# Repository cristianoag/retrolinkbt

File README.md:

# RetroLinkBT
Simple adapter to allow the use of bluetooth joysticks with retro computers

## License 

This work is licensed under a [Creative Commons Attribution-NonCommercial-ShareAlike 4.0 International License](http://creativecommons.org/licenses/by-nc-sa/4.0/).

* If you remix, transform, or build upon the material, you must distribute your contributions under the same license as the original.
* You may not use the material for commercial purposes.
* You must give appropriate credit, provide a link to the license, and indicate if changes were made. You may do so in any reasonable manner, but not in any way that suggests the licensor endorses you or your use.

**ATTENTION**

This project was made for the retro community and not for commercial purposes. So only retro hardware forums and individual people can build this project.

THE SALE OF ANY PART OF THIS PROJECT WITHOUT EXPRESS AUTHORIZATION IS PROHIBITED!

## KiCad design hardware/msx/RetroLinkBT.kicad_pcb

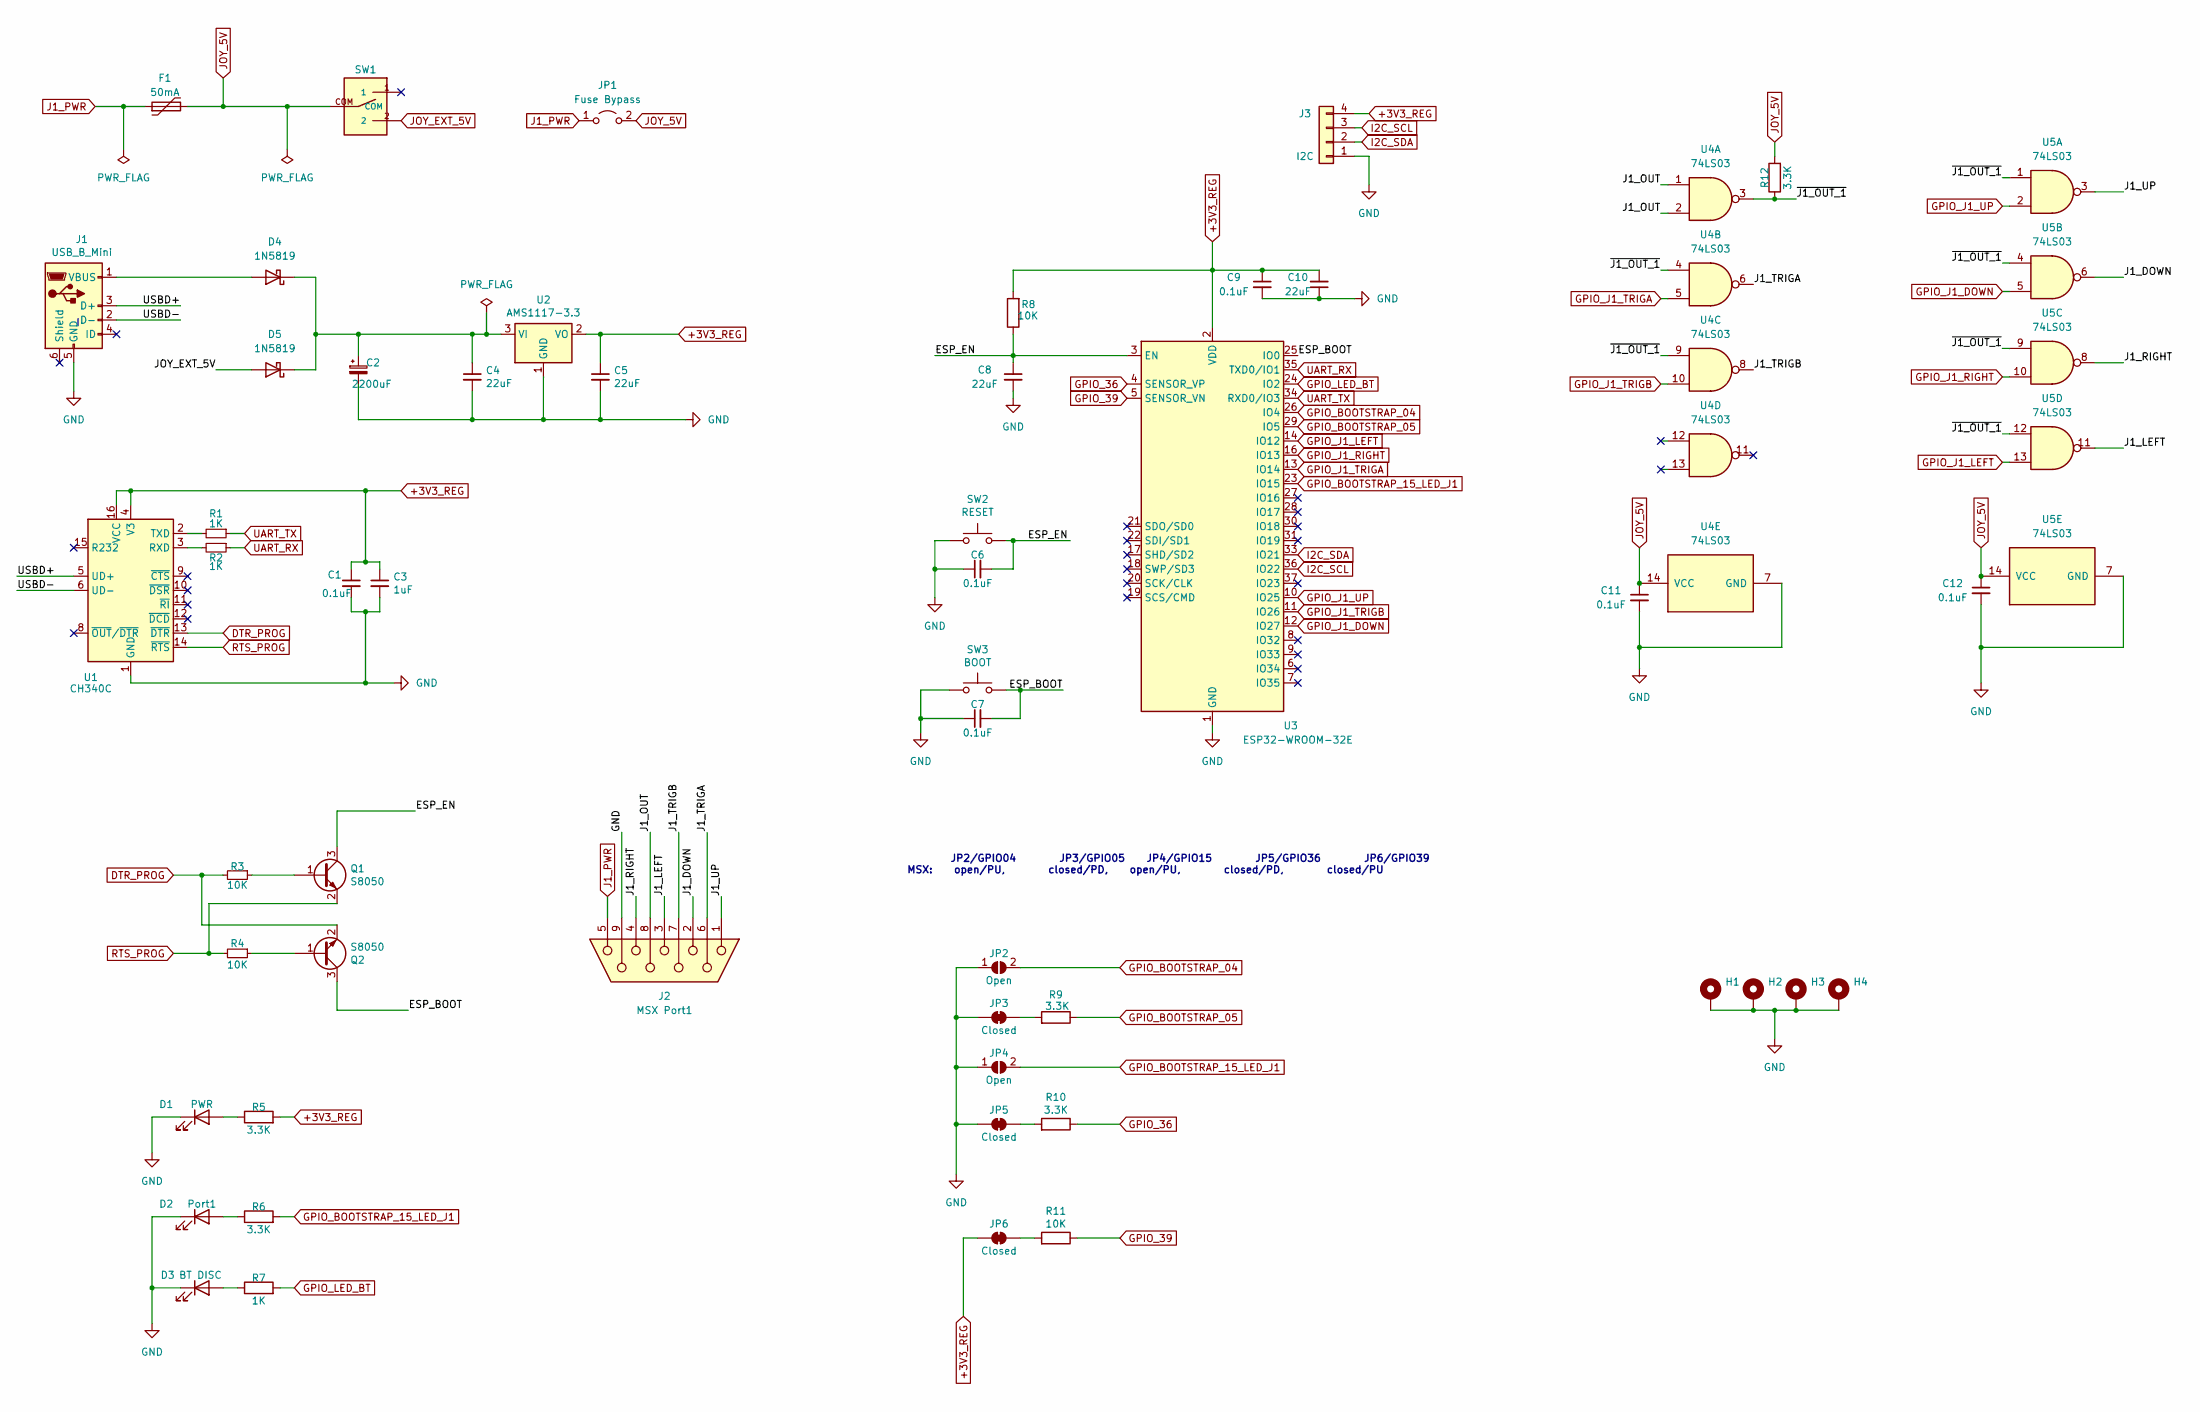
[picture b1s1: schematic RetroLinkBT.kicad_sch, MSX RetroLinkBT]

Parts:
C1, C6, C7, C9, C11, C12: 0.1uF; C_0603_1608Metric_Pad1.08x0.95mm_HandSolder
C2: 2200uF; CP_Elec_10x10.5
C3: 1uF; C_0603_1608Metric_Pad1.08x0.95mm_HandSolder
C4, C5, C8, C10: 22uF; C_0603_1608Metric_Pad1.08x0.95mm_HandSolder
D1: PWR; LED_0805_2012Metric_Pad1.15x1.40mm_HandSolder
D2: Port1; LED_0805_2012Metric_Pad1.15x1.40mm_HandSolder
D3: BT DISC; LED_0805_2012Metric_Pad1.15x1.40mm_HandSolder
D4, D5: 1N5819; D_SOD-123
F1: 50mA; Fuse_1206_3216Metric_Pad1.42x1.75mm_HandSolder
H1, H2, H3, H4: MountingHole_Pad; MountingHole_3.2mm_M3
J1: USB_B_Mini; USB_Mini-B_Lumberg_2486_01_Horizontal
J2: MSX Port1; DSUB-9_Female_Horizontal_P2.77x2.84mm_EdgePinOffset4.94mm_H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
J3: I2C; JST_PH_B4B-PH-K_1x04_P2.00mm_Vertical
JP1: Fuse Bypass; PinHeader_1x02_P2.54mm_Vertical
JP2, JP4: Open; SolderJumper-2_P1.3mm_Open_RoundedPad1.0x1.5mm
JP3, JP5, JP6: Closed; SolderJumper-2_P1.3mm_Bridged_RoundedPad1.0x1.5mm
Q1, Q2: S8050; SOT-23
R1, R2: 1K; R_0603_1608Metric_Pad0.98x0.95mm_HandSolder
R3, R4, R8, R11: 10K; R_0603_1608Metric_Pad0.98x0.95mm_HandSolder
R5, R9, R10: 3.3K; R_0603_1608Metric_Pad0.98x0.95mm_HandSolder
R6, R12: 3.3K; R_0603_1608Metric_Pad0.98x0.95mm_HandSolder; LCSC C4310
R7: 1K; R_0603_1608Metric_Pad0.98x0.95mm_HandSolder; LCSC C4310
SW1: SK12D07VG4
SW2: RESET; SW_SPST_TL3342
SW3: BOOT; SW_SPST_TL3342
U1: CH340C; SOIC-16_3.9x9.9mm_P1.27mm
U2: AMS1117-3.3; SOT-223-3_TabPin2
U3: ESP32-WROOM-32E; LCSC C701341
U4, U5: 74LS03; SOIC-14_3.9x8.7mm_P1.27mm

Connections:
+3V3_REG: C1.1, C3.1, C5.1, C9.1, C10.2, J3.4, JP6.1 (A), R5.2, R8.2, U1.4 (V3), U1.16 (VCC), U2.2 (VO), U3.2 (VDD)
/ESP_BOOT: C7.2, Q2.3 (C), SW3.2, U3.25 (IO0)
/ESP_EN: C6.2, C8.1, Q1.3 (C), R8.1, SW2.2, U3.3 (EN)
/J1_DOWN: J2.2, U5.6
/J1_LEFT: J2.3, U5.11
/J1_OUT: J2.8, U4.1, U4.2
/J1_RIGHT: J2.4, U5.8
/J1_TRIGA: J2.6, U4.6
/J1_TRIGB: J2.7, U4.8
/J1_UP: J2.1, U5.3
/USBD+: J1.3 (D+), U1.5 (UD+)
/USBD-: J1.2 (D-), U1.6 (UD-)
/~J1_OUT_1: R12.1, U4.3, U4.4, U4.9, U5.1, U5.4, U5.9, U5.12
DTR_PROG: Q2.2 (E), R3.2, U1.13 (~DTR)
GND: C1.2, C2.2, C3.2, C4.2, C5.2, C6.1, C7.1, C8.2, C9.2, C10.1, C11.2, C12.2, D1.1 (K), D2.1 (K), D3.1 (K), H1.1, H2.1, H3.1, H4.1, J1.5 (GND), J2.9, J3.1, JP2.1 (A), JP3.1 (A), JP4.1 (A), JP5.1 (A), SW2.1, SW3.1, U1.1 (GND), U2.1 (GND), U3.1 (GND), U3.15 (GND), U3.38 (GND), U3.39 (GND), U4.7 (GND), U5.7 (GND)
GPIO_36: R10.1, U3.4 (SENSOR_VP)
GPIO_39: R11.1, U3.5 (SENSOR_VN)
GPIO_BOOTSTRAP_04: JP2.2 (B), U3.26 (IO4)
GPIO_BOOTSTRAP_05: R9.1, U3.29 (IO5)
GPIO_BOOTSTRAP_15_LED_J1: JP4.2 (B), R6.2, U3.23 (IO15)
GPIO_J1_DOWN: U3.12 (IO27), U5.5
GPIO_J1_LEFT: U3.14 (IO12), U5.13
GPIO_J1_RIGHT: U3.16 (IO13), U5.10
GPIO_J1_TRIGA: U3.13 (IO14), U4.5
GPIO_J1_TRIGB: U3.11 (IO26), U4.10
GPIO_J1_UP: U3.10 (IO25), U5.2
GPIO_LED_BT: R7.2, U3.24 (IO2)
I2C_SCL: J3.3, U3.36 (IO22)
I2C_SDA: J3.2, U3.33 (IO21)
J1_PWR: F1.1, J2.5, JP1.1 (A)
JOY_5V: C11.1, C12.1, F1.2, JP1.2 (B), R12.2, SW1.COM, U4.14 (VCC), U5.14 (VCC)
JOY_EXT_5V: D5.2 (A), SW1.2
unnamed: D1.2 (A), R5.1
unnamed: D2.2 (A), R6.1
unnamed: D3.2 (A), R7.1
unnamed: D4.2 (A), J1.1 (VBUS)
unnamed: C2.1, C4.1, D4.1 (K), D5.1 (K), U2.3 (VI)
unnamed: JP3.2 (B), R9.2
unnamed: JP5.2 (B), R10.2
unnamed: JP6.2 (B), R11.2
unnamed: Q1.1 (B), R3.1
unnamed: Q2.1 (B), R4.1
unnamed: R2.2, U1.3 (RXD)
unnamed: R1.2, U1.2 (TXD)
RTS_PROG: Q1.2 (E), R4.2, U1.14 (~RTS)
UART_RX: R2.1, U3.35 (TXD0/IO1)
UART_TX: R1.1, U3.34 (RXD0/IO3)

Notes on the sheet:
JP2/GPIO04 JP3/GPIO05 JP4/GPIO15 JP5/GPIO36 JP6/GPIO39 MSX: open/PU, closed/PD, open/PU, closed/PD, closed/PU

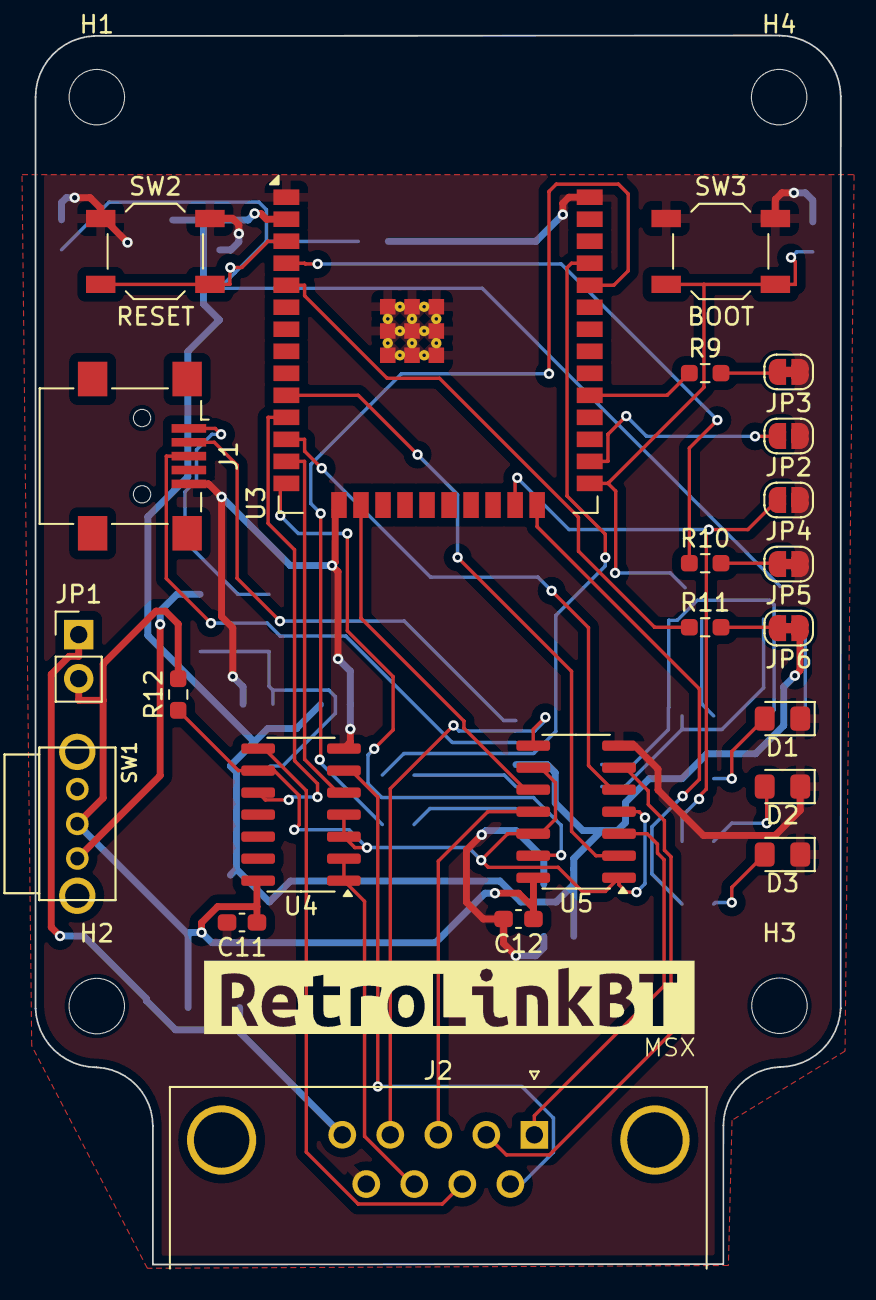
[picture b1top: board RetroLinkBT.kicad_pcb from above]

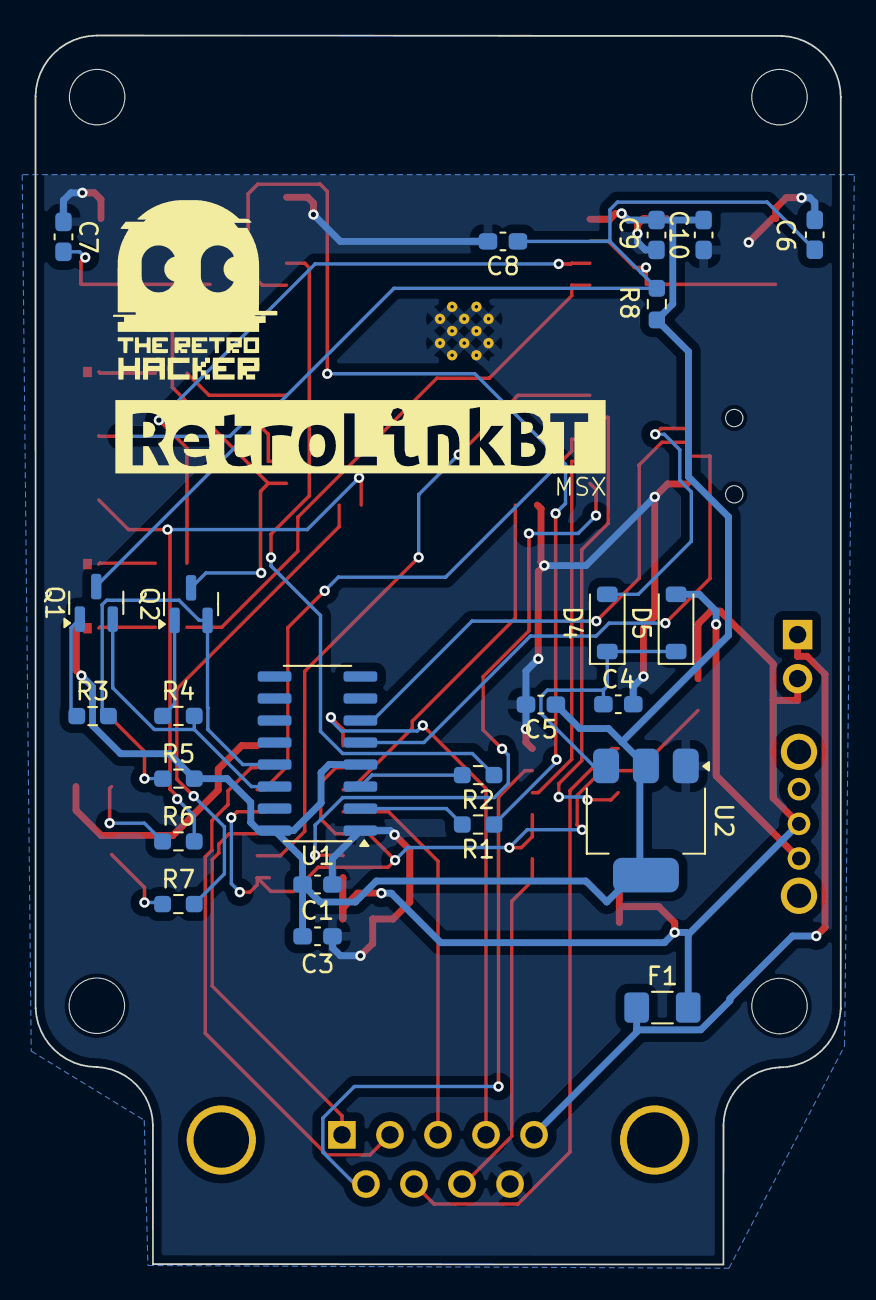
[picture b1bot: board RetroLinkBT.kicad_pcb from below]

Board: 2 copper layers, 46.5 x 70.9 mm, 53 parts (25 on the bottom side), 45 nets.

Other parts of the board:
kibuzzard-673FD7EF, kibuzzard-673FD7EF#2: G***; kibuzzard-673FD7EF

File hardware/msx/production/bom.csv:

Designator,Footprint,Quantity,Value,LCSC Part #
"C1, C11, C12, C6, C7, C9",0603,6,0.1uF,
"C10, C4, C5, C8",0603,4,22uF,
C3,0603,1,1uF,
D1,0805,1,PWR,
D2,0805,1,Port1,
D3,0805,1,BT DISC,
"D4, D5",D_SOD-123,2,1N5819,
F1,1206,1,50mA,
J1,USB_Mini-B_Lumberg_2486_01_Horizontal,1,USB_B_Mini,
J2,DSUB-9_Female_Horizontal_P2.77x2.84mm_EdgePinOffset4.94mm_Housed_MountingHolesOffset7.48mm,1,MSX Port1,
JP1,PinHeader_1x02_P2.54mm_Vertical,1,Fuse Bypass,
"JP2, JP4",SolderJumper-2_P1.3mm_Open_RoundedPad1.0x1.5mm,2,Open,
"Q1, Q2",SOT-23,2,S8050,
"R1, R2",0603,2,1K,
"R10, R5, R9",0603,3,3.3K,
"R11, R3, R4, R8",0603,4,10K,
"R12, R6",0603,2,3.3K,C4310
R7,0603,1,1K,C4310
SW1,SK12D07VG4,1,SK12D07VG4,
SW2,SW_SPST_TL3342,1,RESET,
SW3,SW_SPST_TL3342,1,BOOT,
U1,SOIC-16_3.9x9.9mm_P1.27mm,1,CH340C,
U2,SOT-223-3_TabPin2,1,AMS1117-3.3,
U3,ESP32-WROOM-32E,1,ESP32-WROOM-32E,C701341
"U4, U5",SOIC-14_3.9x8.7mm_P1.27mm,2,74LS03,

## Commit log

2024-11-22 initial upload
